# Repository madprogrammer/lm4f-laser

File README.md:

lm4f-laser
==========

Laser projector based on Stellaris Launchpad, a custom DAC board with AD7249BRZ 12-bit serial DAC
and a pair of 20Kpps galvo scanners from eBay.

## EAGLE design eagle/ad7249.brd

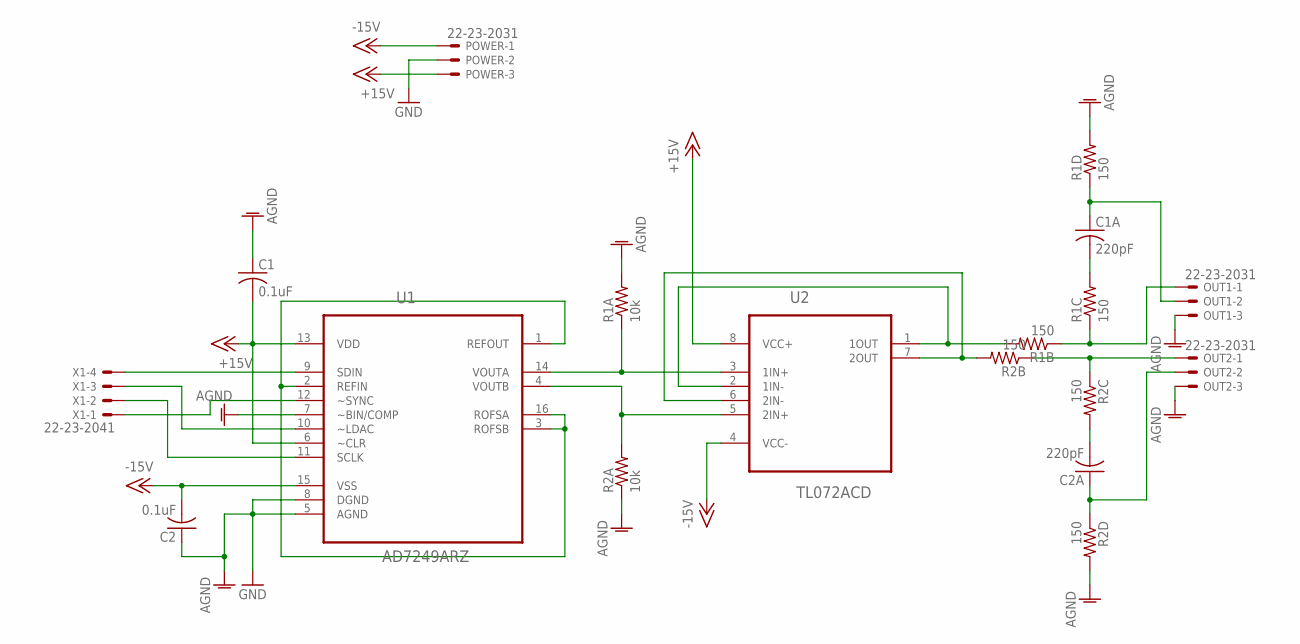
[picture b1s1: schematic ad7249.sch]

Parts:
C1, C2: 0.1uF; C1206
C1A, C2A: 220pF; C1206
OUT1, OUT2: 22-23-2031
POWER: 22-23-2031; MPN 22-23-2031
R1A, R2A: 10k; R1206
R1B, R1C, R1D, R2B, R2C, R2D: 150; R1206
U1: AD7249ARZ; SOIC127P1042X272-16N
U2: TL072ACD; SOIC127P600X175-8N
X1: 22-23-2041

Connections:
+15V: C1.2, POWER.3, U1.6 (~CLR), U1.13 (VDD), U2.8 (VCC+)
-15V: C2.2, POWER.1, U1.15 (VSS), U2.4 (VCC-)
AGND: C1.1, C2.1, OUT1.3, OUT2.3, POWER.2, R1A.2, R1D.2, R2A.1, R2D.2, U1.5 (AGND), U1.7 (~BIN/COMP), U1.8 (DGND)
unnamed: U1.1 (REFOUT), U1.2 (REFIN), U1.3 (ROFSB), U1.16 (ROFSA)
unnamed: R1A.1, U1.14 (VOUTA), U2.3 (1IN+)
unnamed: R2A.2, U1.4 (VOUTB), U2.5 (2IN+)
unnamed: OUT2.1, R2B.1, R2C.1
unnamed: U1.9 (SDIN), X1.4
unnamed: R1B.2, U2.1 (1OUT), U2.2 (1IN-)
unnamed: R2B.2, U2.6 (2IN-), U2.7 (2OUT)
unnamed: C2A.2, R2C.2
unnamed: U1.11 (SCLK), X1.2
unnamed: C1A.2, R1C.2
unnamed: C2A.1, OUT2.2, R2D.1
unnamed: C1A.1, OUT1.2, R1D.1
unnamed: OUT1.1, R1B.1, R1C.1
unnamed: U1.10 (~LDAC), X1.3
unnamed: U1.12 (~SYNC), X1.1

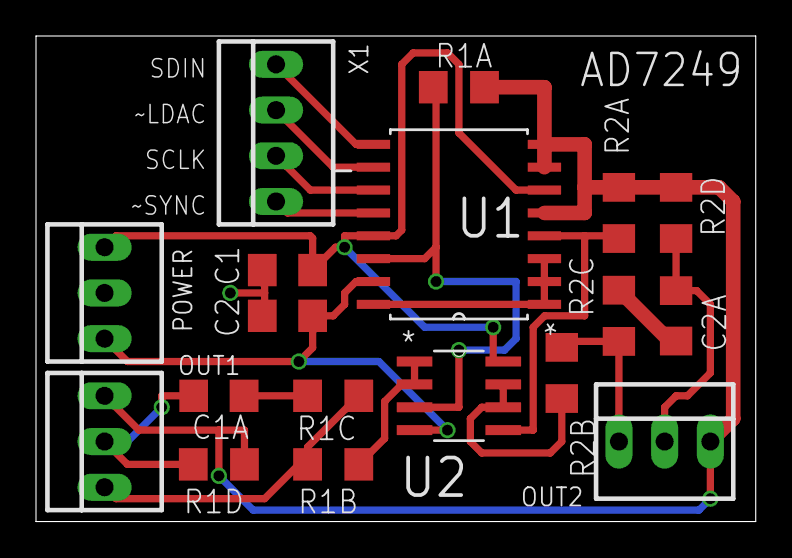
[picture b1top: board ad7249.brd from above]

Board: 2 copper layers, 40.0 x 27.0 mm, 18 parts (0 on the bottom side), 18 nets.

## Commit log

2014-06-07 add eagle board & schematic
